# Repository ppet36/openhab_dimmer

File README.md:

# OpenHAB dimmer(s)

This repository contains simple dimmers for LED lighting based on potentiometer or cheap
chinese RF LED controller such as
http://www.ebay.com/itm/Mini-12V-RF-Wireless-Remote-Switch-Controller-Dimmer-for-LED-Strip-Light.

As always is there Cadsoft's Eagle schematic, PCB and firmware for ESP8266 that can be programmed using Arduino IDE.
Potentiometer version uses Average library https://github.com/MajenkoLibraries/Average for nice fade efect and jitter elimination.

Both dimmers are based on MOSFET transistor at output and cheap DC/DC converter with LM2596 from eBay (set at 3.3V!!!) for powering ESP.
In my case i used IPA040N06N with 0.004ohm resistance in threshold state. PWM frequency is set only to 120Hz so any MOSFET with
reasonable parameters can be used.

Like other my OpenHAB projects is there set of default parameters in firmare as well as HTML configuration interface at IP address of device.

## Potentiometer version
Potentiometer version uses in my case slider potentiometer and ESP07 with ADC input.

## RF version
RF version uses standard receiver available from eBay such as http://www.ebay.com/sch/i.html?_nkw=433mhz+receiver. Remote control codes can be set in firmware. This version uses my favorite ESP01 :)

## Some project images
### RF version

### POT version

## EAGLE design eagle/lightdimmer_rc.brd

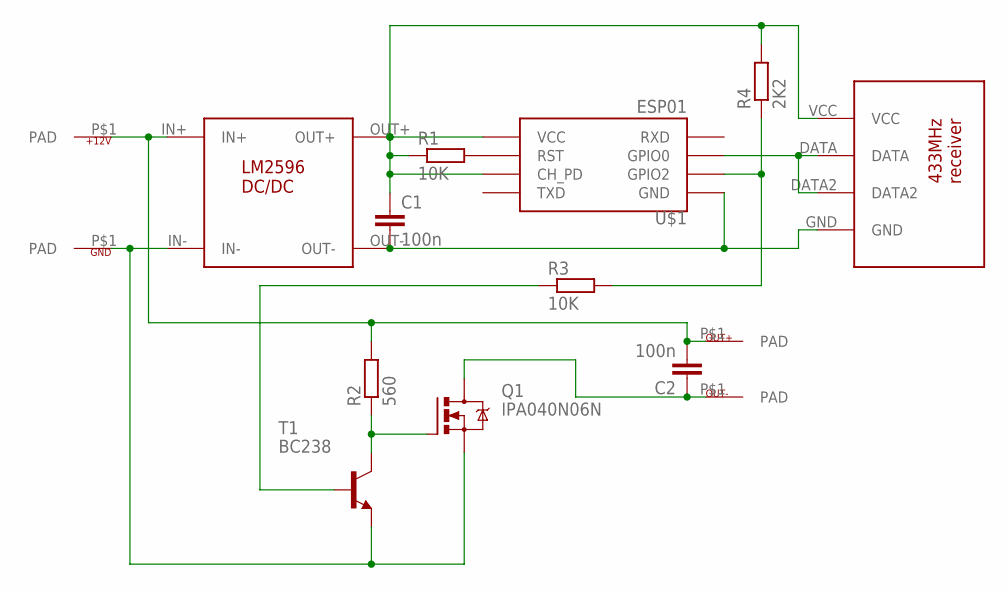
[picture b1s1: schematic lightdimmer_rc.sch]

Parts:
+12V: PAD
C1, C2: 100n; C050-025X075
GND: PAD
OUT+: PAD
OUT-: PAD
Q1: IPA040N06N; TO220BV
R1, R3: 10K; 0204/7
R2: 560; 0204/7
R4: 2K2; 0204/7
T1: BC238; TO92-CBE
U$1: ESP01
U$2: RECV433MHZ
U$3: LM2596DCDC

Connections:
unnamed: C1.1, R1.1, R4.2, U$1.CH_PD, U$1.VCC, U$2.VCC, U$3.OUT+
unnamed: C1.2, U$1.GND, U$2.GND, U$3.OUT-
unnamed: U$1.GPIO0, U$2.DATA, U$2.DATA2
unnamed: C2.1, OUT-.P$1, Q1.D
unnamed: GND.P$1, Q1.S, T1.E, U$3.IN-
unnamed: Q1.G, R2.1, T1.C
unnamed: +12V.P$1, C2.2, OUT+.P$1, R2.2, U$3.IN+
unnamed: R3.2, R4.1, U$1.GPIO2
unnamed: R1.2, U$1.RST
unnamed: R3.1, T1.B

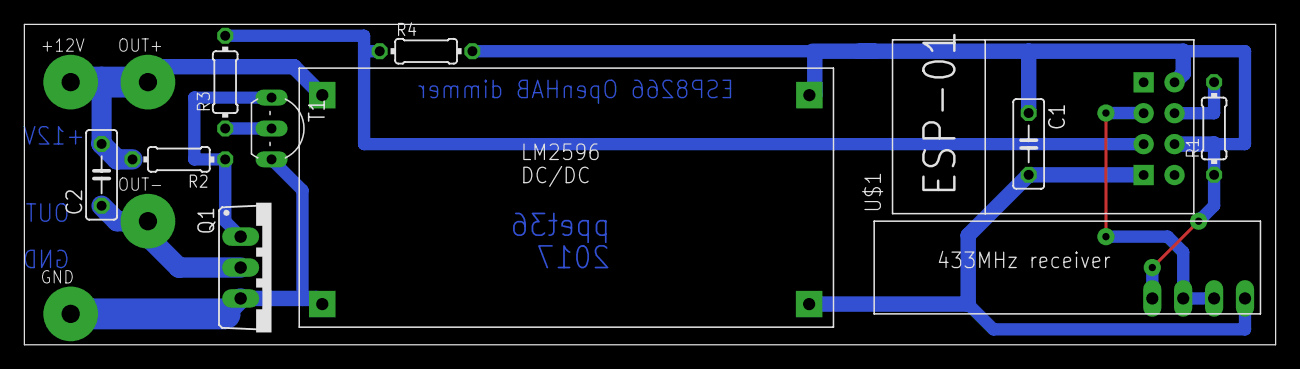
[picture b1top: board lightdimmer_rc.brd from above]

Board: 2 copper layers, 102.8 x 26.3 mm, 15 parts (0 on the bottom side), 10 nets.

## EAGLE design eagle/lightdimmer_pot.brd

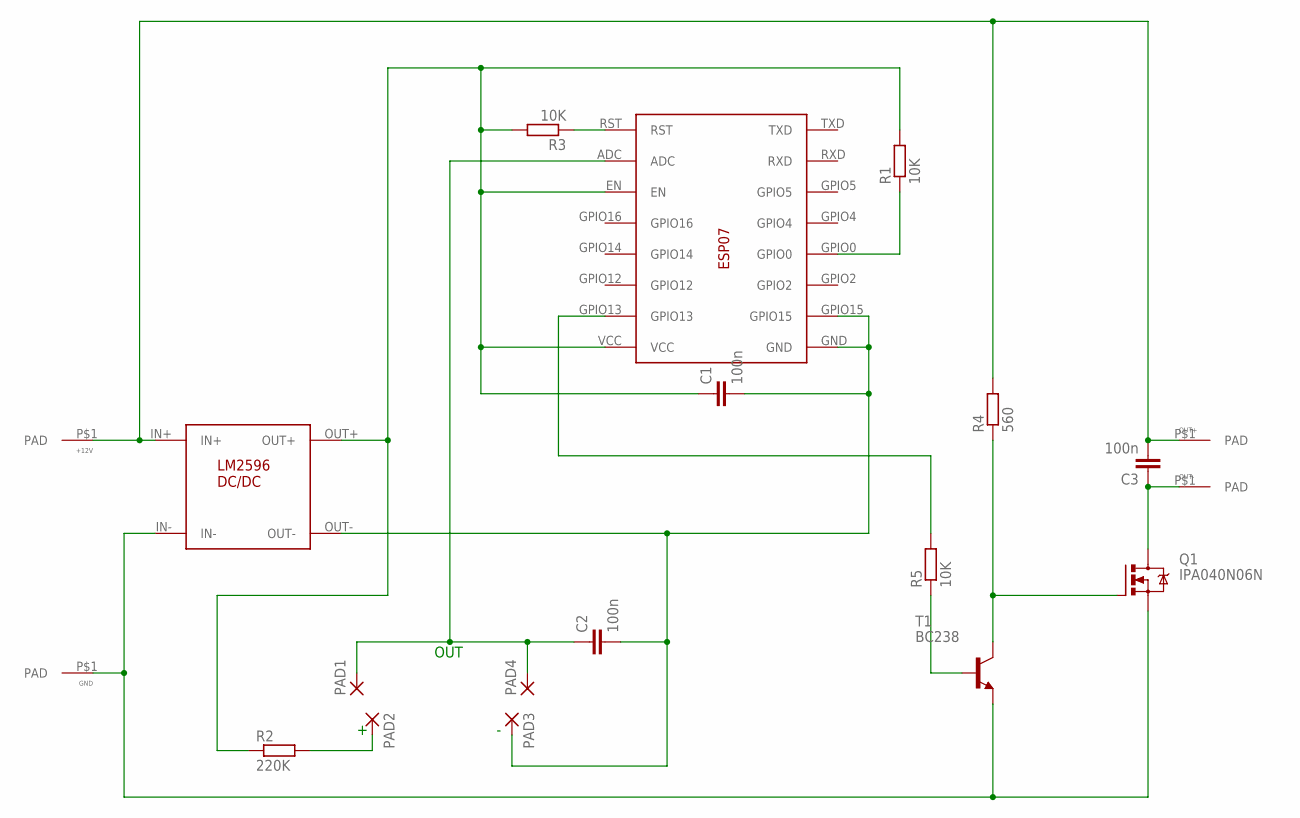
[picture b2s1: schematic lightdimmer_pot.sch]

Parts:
+12V: PAD
C1, C2, C3: 100n; C050-025X075
GND: PAD
OUT+: PAD
OUT-: PAD
PAD1, PAD2, PAD3, PAD4: WIREPAD3,17/1,1; 3,17/1,1
Q1: IPA040N06N; TO220BV
R1, R3, R5: 10K; 0204/7
R2: 220K; 0204/7
R4: 560; 0204/7
T1: BC238; TO92-CBE
U$1: LM2596DCDC
U$2: ESP07

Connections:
unnamed: GND.P$1, Q1.S, T1.E, U$1.IN-
unnamed: +12V.P$1, C3.2, OUT+.P$1, R4.2, U$1.IN+
unnamed: C3.1, OUT-.P$1, Q1.D
unnamed: C1.2, C2.2, PAD3.1, U$1.OUT-, U$2.GND, U$2.GPIO15
unnamed: C1.1, R1.2, R2.1, R3.2, U$1.OUT+, U$2.EN, U$2.VCC
unnamed: R5.2, U$2.GPIO13
unnamed: Q1.G, R4.1, T1.C
unnamed: C2.1, PAD1.1, PAD4.1, U$2.ADC
unnamed: R1.1, U$2.GPIO0
unnamed: R5.1, T1.B
unnamed: PAD2.1, R2.2
unnamed: R3.1, U$2.RST

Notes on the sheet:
OUT

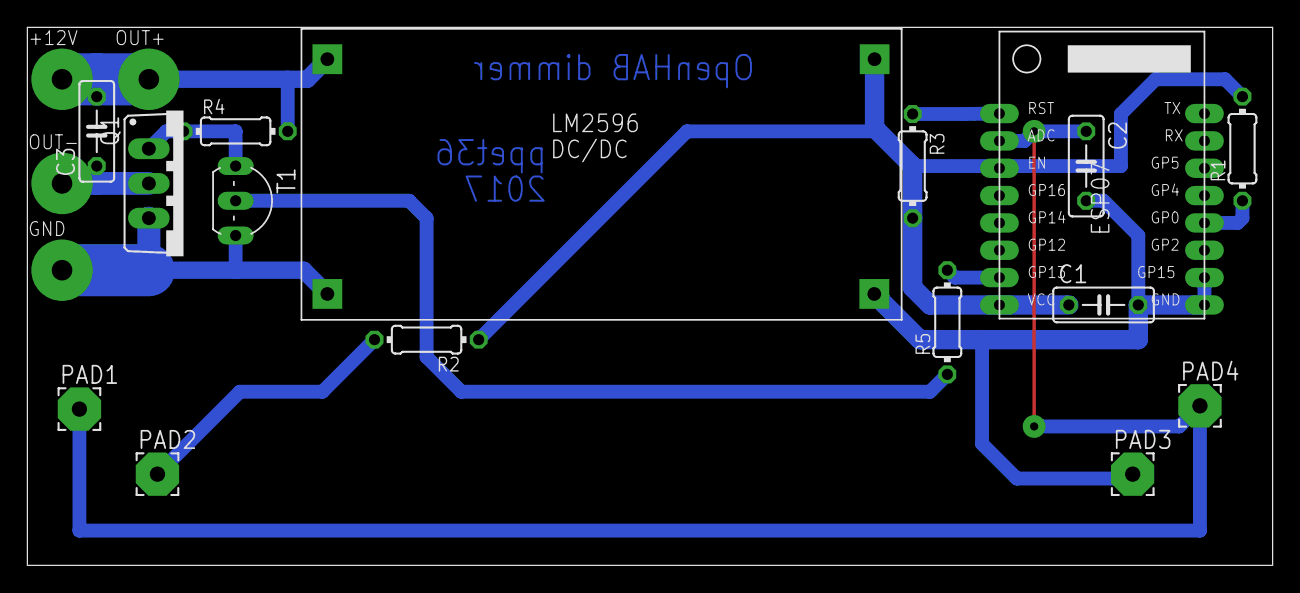
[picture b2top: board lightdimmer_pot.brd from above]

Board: 2 copper layers, 91.1 x 39.4 mm, 20 parts (0 on the bottom side), 12 nets.

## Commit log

2017-01-22 Updated to actual version
